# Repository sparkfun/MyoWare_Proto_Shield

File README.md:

MyoWare™ Proto Shield
========================================

[*SparkFun Part Name (SKU)*](URL for product on Sparkfun.com)

The MyoWare™ Proto Shield is designed to pair with the MyoWare™ Muscle Sensor. This shield provides 8 x 15 solderable through holes on a standard 0.1" grid.

Repository Contents
-------------------

* **/Hardware** - Eagle design files (.brd, .sch)

Documentation
--------------
* **[Library](GitHub library URL)** - <LANGUAGE> library for the <PRODUCT NAME>.
* **[Hookup Guide](Learn.SparkFun URL)** - Basic hookup guide for the <PRODUCT NAME>.
* **[SparkFun Fritzing repo](https://github.com/sparkfun/Fritzing_Parts)** - Fritzing diagrams for SparkFun products.
* **[SparkFun 3D Model repo](https://github.com/sparkfun/3D_Models)** - 3D models of SparkFun products.

Product Versions
----------------
* [v1.0](part URL)- MyoWare™ Proto Shield

License Information
-------------------

This product is _**open source**_!

Please review the LICENSE.md file for license information.

If you have any questions or concerns on licensing, please contact techsupport@sparkfun.com.

Distributed as-is; no warranty is given.

- Your friends at SparkFun.

_<COLLABORATION CREDIT>_

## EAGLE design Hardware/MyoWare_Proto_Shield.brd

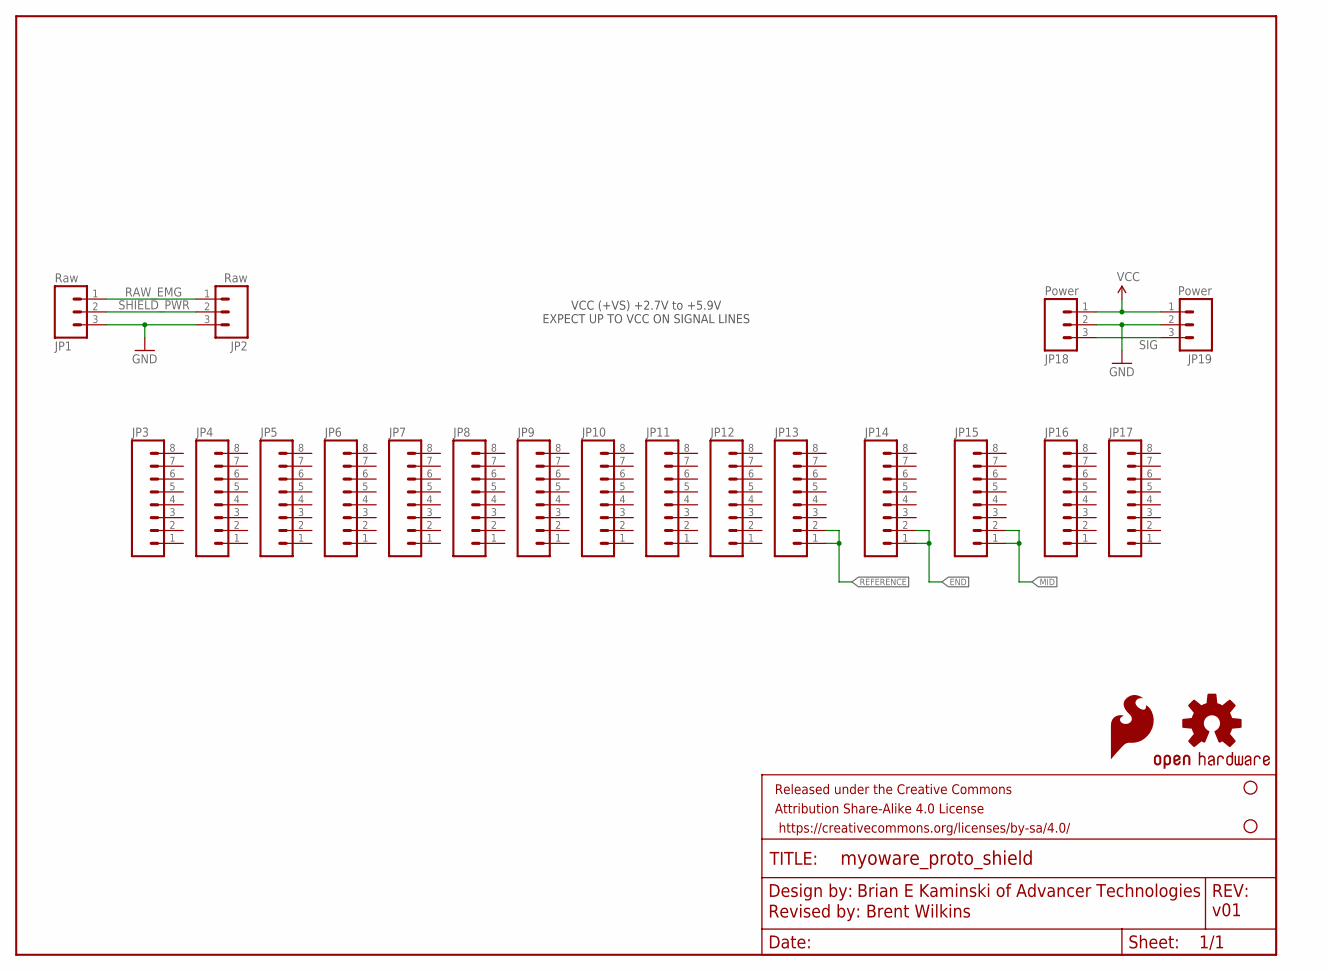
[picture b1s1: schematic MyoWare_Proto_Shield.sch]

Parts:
FRAME1: FRAME-LETTER; CREATIVE_COMMONS
JP1, JP2: Raw; 1X03_NO_SILK
JP3, JP4, JP5, JP6, JP7, JP8, JP9, JP10, JP11, JP12, JP13, JP14, JP15, JP16, JP17: M08NO_SILK; 1X08_NO_SILK
JP18, JP19: Power; 1X03_NO_SILK
JP20, JP21: STAND-OFF
LOGO1: SFE_LOGO_FLAME.1_INCH; SFE_LOGO_FLAME_.1
LOGO2: OSHW-LOGOS; OSHW-LOGO-S

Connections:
END: JP14.1, JP14.2
GND: JP1.3, JP2.3, JP18.2, JP19.2
MID: JP15.1, JP15.2
RAW_EMG: JP1.1, JP2.1
REFERENCE: JP13.1, JP13.2
SHIELD_PWR: JP1.2, JP2.2
SIG: JP18.3, JP19.3
VCC: JP18.1, JP19.1

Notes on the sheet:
Brian E Kaminski of Advancer Technologies
Revised by: Brent Wilkins
v01
VCC (+VS) +2.7V to +5.9V EXPECT UP TO VCC ON SIGNAL LINES

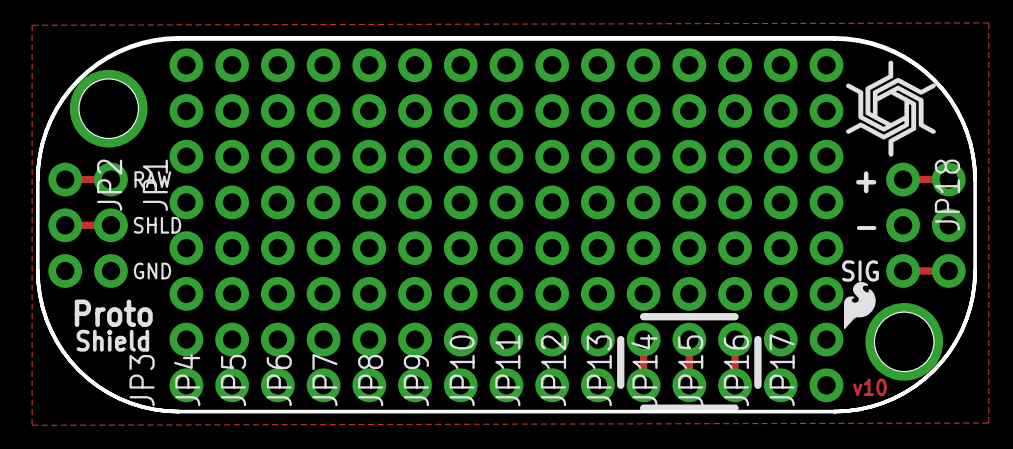
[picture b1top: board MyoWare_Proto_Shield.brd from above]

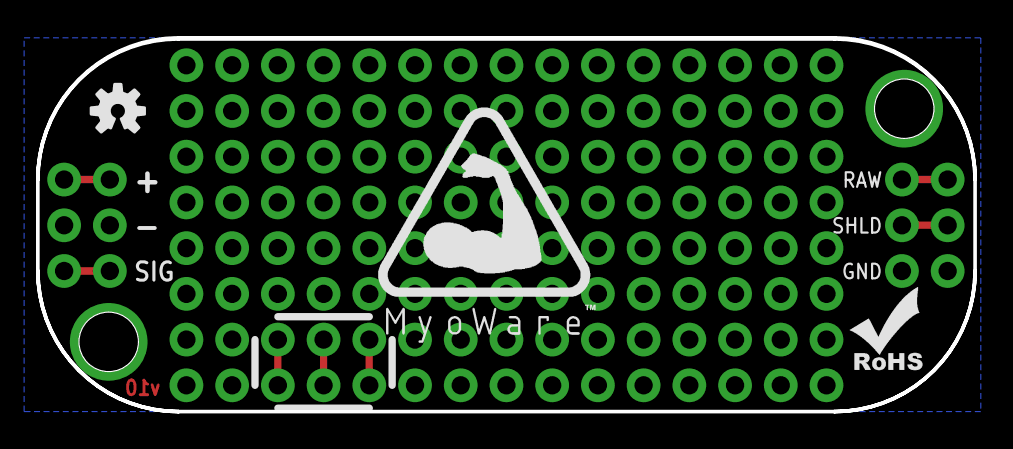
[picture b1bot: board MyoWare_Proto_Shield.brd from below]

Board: 2 copper layers, 52.1 x 20.8 mm, 27 parts (3 on the bottom side), 8 nets.

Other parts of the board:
U$1: MYOWARE_LOGO
U$3: ROHS
U$9: SPIRAL_LOGO_60%

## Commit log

2015-07-09 Tweaks to meet SFE checklist
2015-07-10 Copied remote silk to bottom
2015-07-13 Removed fiducials
2015-08-05 Updated version to 10
2015-08-05 Moved diameter dimension from dimension layer
2015-09-21 Removed RoHS compliance claim

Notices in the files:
parts and their libraries:
SparkFun-Connectors: Licensing: CC v3.0 Share-Alike You are welcome to use this library for commercial purposes.
SparkFun-Aesthetics: Licensing: Creative Commons ShareAlike 4.0 International - https://creativecommons.org/licenses/by-sa/4.0
SparkFun-Aesthetics: Released under the Creative Commons
